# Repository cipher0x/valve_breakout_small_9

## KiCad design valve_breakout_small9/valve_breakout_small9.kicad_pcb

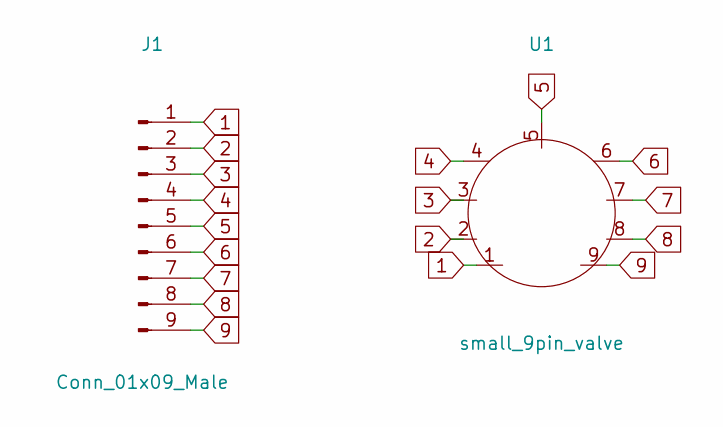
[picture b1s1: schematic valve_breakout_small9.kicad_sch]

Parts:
J1: Conn_01x09_Male; PinSocket_1x09_P2.54mm_Vertical
U1: small_9pin_valve; small9_valve

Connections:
1: J1.1, U1.1
2: J1.2, U1.2
3: J1.3, U1.3
4: J1.4, U1.4
5: J1.5, U1.5
6: J1.6, U1.6
7: J1.7, U1.7
8: J1.8, U1.8
9: J1.9, U1.9

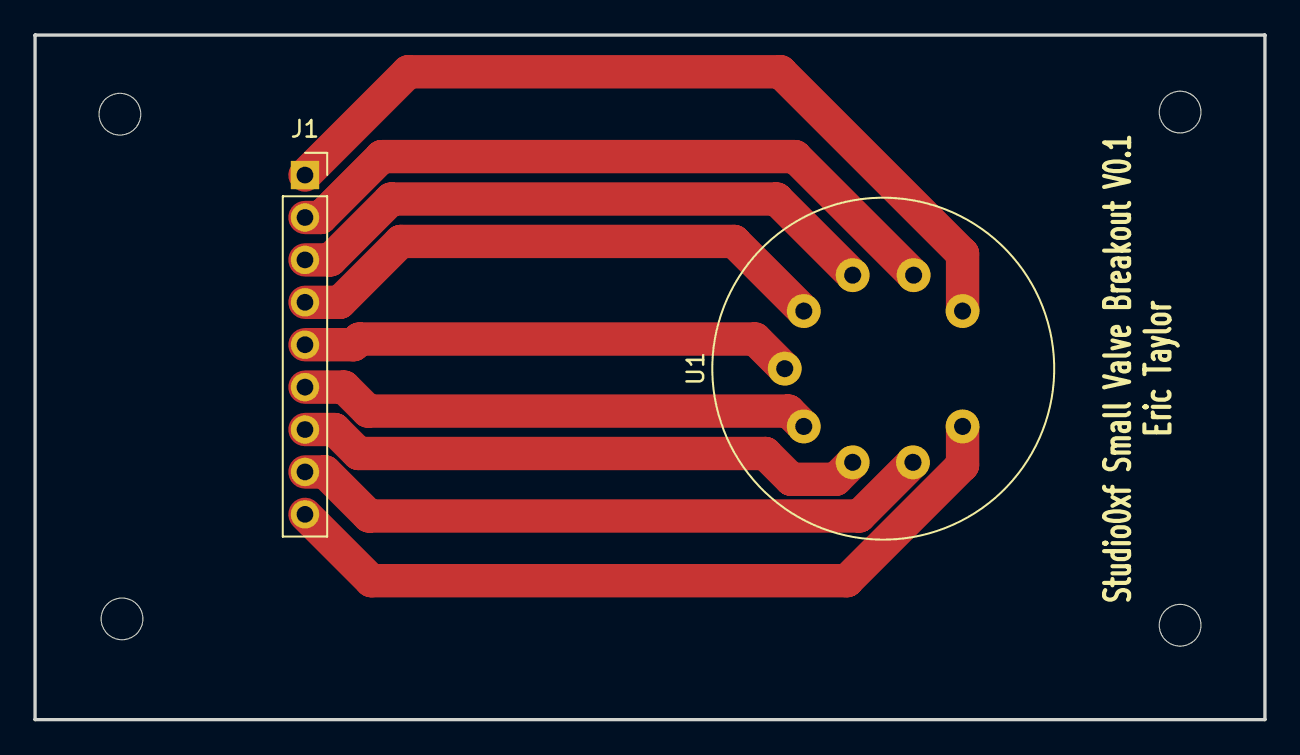
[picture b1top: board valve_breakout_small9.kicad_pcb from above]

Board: 2 copper layers, 73.7 x 41.0 mm, 3 parts (0 on the bottom side), 9 nets.

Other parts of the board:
REF: MountingHole_2.5mm

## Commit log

2023-01-16 init
